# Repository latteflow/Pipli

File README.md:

# Pipli \- Medicine reminder device for elderly people.

A Device to help elderly people  
Github link: [https://github.com/latteflow/Pipli](https://github.com/latteflow/Pipli)  
Drawio file: 

Contributors: Nandani & Latteflow Team   
Started on: 21 January 2025

## Problem Statement 

Nowadays, most elderly people live alone at home. They often cannot leave because they are emotionally attached to their homes. However, living alone makes it difficult for them to take care of themselves. 

To solve this problem, we can create a low-cost device that provides timely reminders for meals and medication. This device can be worn on the wrist like a watch, making it easy to carry and use. It uses a low-cost microcontroller and a small ubiquitous replaceable battery. It can be easily connected to a smartphone via Bluetooth, where the reminders can be pre-programmed and saved in advance. The device will be easily accessible, ensuring elderly individuals receive important reminders without hassle.

The design and the code will be made open-source, such that everyone can access and easily replicate the design to help. 

We can create a device app called Pipli, which will feature a reminder system for important notifications. This app is designed to be highly convenient for elderly users, ensuring that they can easily set and receive reminders for various tasks and events. By focusing on a user-friendly interface with large buttons and clear instructions, Pipli will cater specifically to the needs of seniors, helping them manage their daily schedules effectively.

Approach 

![][image1]

This device will have a note chart for important items such as medication and food reminders. We can create a mockup of the app using Figma to ensure that everything is easy to understand. The app will include several features, such as buttons for help, sound notifications, feedback, and options for listening, downloading, or sharing information. This design will enhance user experience and make it more accessible for elderly users.

Do UX mockup of the app on the Figma 

1 Start writing a detailed approach 

- [ ] What is required   
- [ ] A smartphone with an application   
- [ ] Customizable options such as \- Repeat intervals, Advance alerts and Sound notifications.  
- [ ] A Pipli device to manage 

2 What functionality will the device have 

- [ ] Haptic feedback, ie, vibration   
- [ ] Sound   
- [ ] A button for Help  
- [ ] A button to listen   
- [ ] To create a new note  
- [ ] Delete Option  
- [ ] Share Option   
- [ ] Download Option

3 What components will it have 

- [ ] An MCU with WiFi/Bluetooth  
- [ ] Vibration motor   
- [ ] Sound   
- [ ] Button 

## 

## Electronics

Once each sensor and actuator has been tested and programmed individually, we have to design a PCB, which needs to be printed.   
Finally, we will solder every component and test it. When everything is working, then we will incorporate it into the mechanical housing 

KiCAD: [https://www.kicad.org/](https://www.kicad.org/)

![][image2]  
 Example PCB 

## Firmware

For programming and all: [https://platformio.org/](https://platformio.org/)

It has an extension for VS Code, please sign up and try to get it working

Website to simulate and run your program: [https://wokwi.com/esp32](https://wokwi.com/esp32)

## Mechanical Design 

Autodesk Fusion:   
[https://www.autodesk.com/in/products/fusion-360/overview](https://www.autodesk.com/in/products/fusion-360/overview)

Once the electronics are ready, we will start the mechanical design process. We will be utilizing the 3D printer for design iterations. 

Meanwhile, you should start designing the sketch, iterate, and think about user interactions and user experience. 

![][image3]

A Mockup of the Pipli device with Buttons

Fusion 360 Link for the design: 

[https://a360.co/4kiht4b](https://a360.co/4kiht4b)

## Application

Android / IOS   
[https://reactnative.dev/](https://reactnative.dev/)

We will have an app which will let the user connect and configure the reminders. It will be a primary way to connect to the device and save the program and reminders. Once the medicine course is over, it can be removed and a new medicine course can be saved for someone else. It will have the ability to connect to multiple devices.  

The app will be created in the React Native framework, such that both Android and IOS devices can work. 

UI / UX 

Figma:   
[https://www.figma.com/](https://www.figma.com/)

- [ ] PUT user interaction workflow here   

1. Press a button   
2. The device will wake up   
3. It will try to search for a new device   
4. If there is no device, then it will go into sleep mode   
5. Once the reminder comes close, it will wake up and try to play the sound/vibration sensor   
6. Once the user presses the button confirming they have taken medicine / do the work.   
7. Then it will go to sleep 

The user can ask for help by pressing the button   
If the device wakes and tries to connect with the smartphone, it will play the sound or send a notification that someone is in need of help.

## Components required 

ESP32

Tutorial: [https://randomnerdtutorials.com/projects-esp32/](https://randomnerdtutorials.com/projects-esp32/)

USB micro programmer / UBB C programmer 

LED 

Vibration motor: 

[https://robu.in/product/dc-vibration-motor-module/](https://robu.in/product/dc-vibration-motor-module/)

How to interface vibration motor with sensor: 

[https://thecustomizewindows.com/2021/08/esp32-and-coin-vibrator-motor/](https://thecustomizewindows.com/2021/08/esp32-and-coin-vibrator-motor/) 

Sound sensor: 

[https://www.elprocus.com/sound-sensor-working-and-its-applications/](https://www.elprocus.com/sound-sensor-working-and-its-applications/)

 Sound buzzers: 

[https://esp32io.com/tutorials/esp32-piezo-buzzer](https://esp32io.com/tutorials/esp32-piezo-buzzer)

[https://robu.in/product/5v-active-alarm-buzzer-module-arduino/](https://robu.in/product/5v-active-alarm-buzzer-module-arduino/)

Buttons or Tactile switch: 

[https://robu.in/product/6x6x5-tactile-push-button-switch/](https://robu.in/product/6x6x5-tactile-push-button-switch/)

Rechargeable battery: 

[https://robu.in/product/400mah-pcm-protected-micro-li-po-battery-2/](https://robu.in/product/400mah-pcm-protected-micro-li-po-battery-2/)

Lipo charger with USB C: 

[https://robu.in/product/lipo-charger-with-usc-c-type-jack/](https://robu.in/product/lipo-charger-with-usc-c-type-jack/)

[https://www.flyrobo.in/tp4056-1a-li-ion-lithium-battery-charging-module-with-current-protection-type-c?tracking=ads\&gQT=1](https://www.flyrobo.in/tp4056-1a-li-ion-lithium-battery-charging-module-with-current-protection-type-c?tracking=ads&gQT=1)

[https://robu.in/product/tp4056-1a-li-ion-lithium-battery-charging-module-with-current-protection-type-c/](https://robu.in/product/tp4056-1a-li-ion-lithium-battery-charging-module-with-current-protection-type-c/)

3d Printing service: [https://robu.in/product/3d-printing-service/](https://robu.in/product/3d-printing-service/)

2 List key steps

* Break down the journey into individual steps   
  Pipli Device \- Medicine Remainder  
- [ ] User interaction workflow  
1. Open the  phone go to the  bluetooth option and press the bluetooth  and open and see the Pipli device

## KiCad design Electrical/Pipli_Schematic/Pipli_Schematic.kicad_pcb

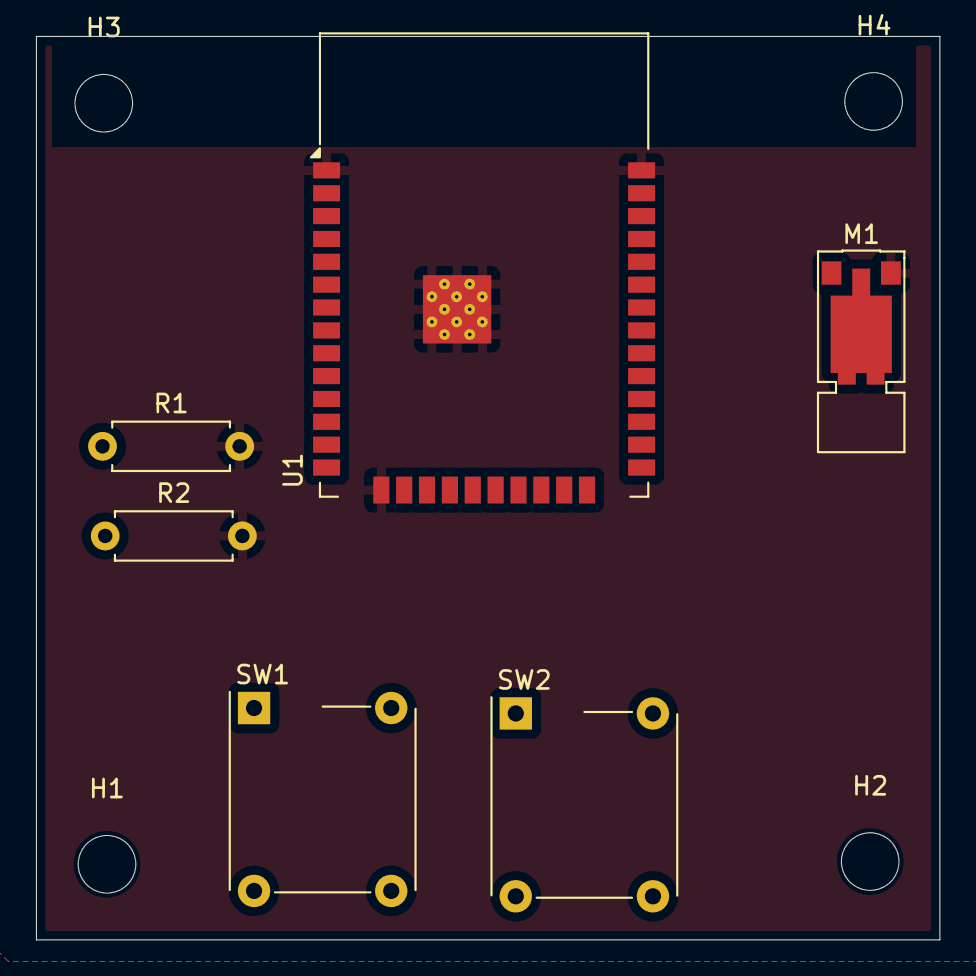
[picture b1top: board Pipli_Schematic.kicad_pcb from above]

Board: 2 copper layers, 50.2 x 50.2 mm, 10 parts (0 on the bottom side), 4 nets, no tracks yet.

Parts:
H1, H2, H3, H4: M3; MountingHole_3.2mm_M3
M1: Motor_DC; Vybronics_VZ30C1T8219732L
R1, R2: 18k; R_Axial_DIN0207_L6.3mm_D2.5mm_P7.62mm_Horizontal
SW1, SW2: SW; SW_MEC_5GTH9
U1: ESP32-WROOM-32D

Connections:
/INPUT_SW_1: R1.1, SW1.1 (A), SW1.2 (A), U1.6 (IO34)
/INPUT_SW_2: R2.1, SW2.1 (A), SW2.2 (A), U1.37 (IO23)
/VIB_POS: M1.1 (+), U1.30 (IO18)
GND: M1.2 (-), R1.2, R2.2, U1.1 (GND), U1.15 (GND), U1.38 (GND), U1.39 (GND)

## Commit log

2025-03-09 write button press code
2025-03-09 add application
2025-03-23 add microbit
2025-03-23 ok blink working
2025-03-23 add esp32 client
2025-03-23 receive working
2025-03-23 app get head start
2025-03-24 add new screen and try to debug bluetooth
2025-03-24 add new files
2025-03-24 remove nordic platform
2025-03-24 name change
2025-03-24 rename folder name
2025-03-25 data parse and data save working
2025-03-25 data parsing working inside readme file
2025-03-26 compile for other board as well
2025-04-16 working proto
2025-04-18 working flawlessly till now: connect & receive
2025-04-18 working till now
2025-04-18 send and recieve string data is working
2025-04-18 working
2025-04-18 basic blinking of on data transfer
2025-04-18 remove useeffect
2025-04-18 create user working
2025-04-18 medication profile working basic
2025-04-18 basic version of app working
2025-04-18 buidl
2025-04-18 modify little bit still working
2025-04-18 before making big change
2025-04-18 ok few things working
2025-04-18 working pefectly
2025-04-18 change from medicine to time specific
2025-04-18 All things working now
2025-04-24 add step file
2025-04-24 time is working
2025-04-24 few things working
2025-04-24 make data chunking
2025-04-24 app is handling the data fine
2025-04-24 remove few things
2025-04-24 add time reminder
2025-04-25 app is working fine
2025-04-25 app working fine
